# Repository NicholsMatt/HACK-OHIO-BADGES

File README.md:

# HACK-OHIO-BADGES
PCB badges for HACK OHI/O X in Autumn 2022

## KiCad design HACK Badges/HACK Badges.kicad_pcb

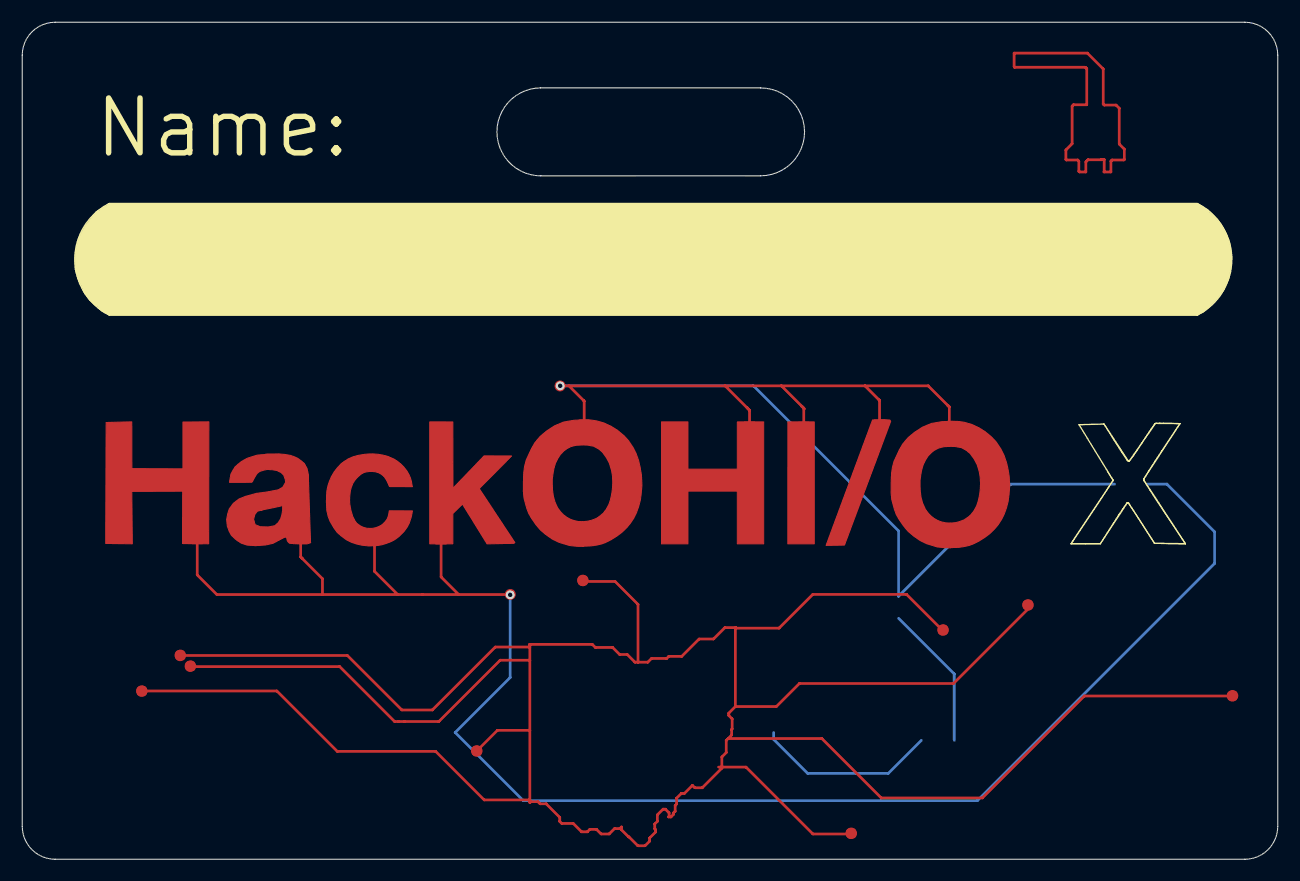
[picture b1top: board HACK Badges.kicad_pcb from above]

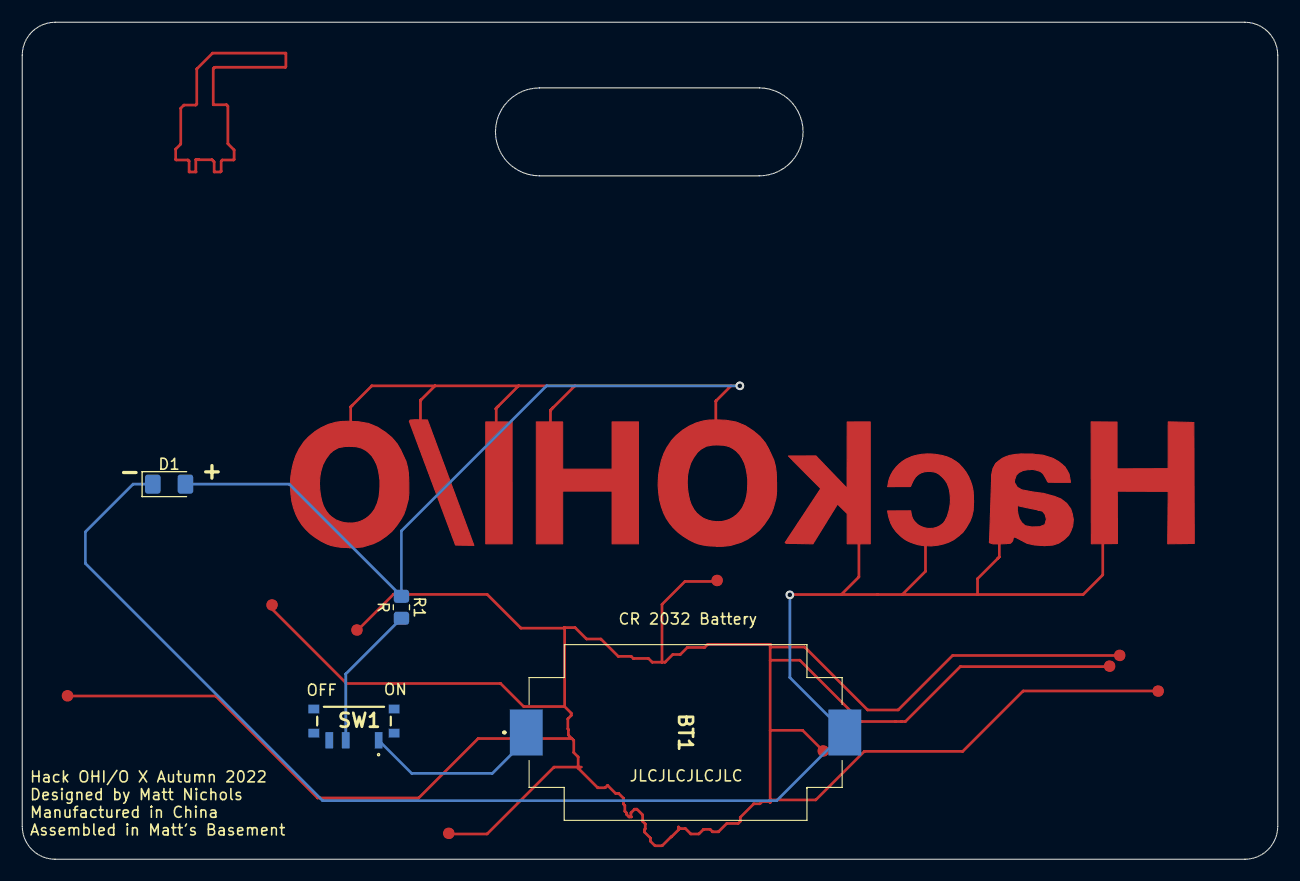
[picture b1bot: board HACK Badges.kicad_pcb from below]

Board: 2 copper layers, 114.3 x 76.2 mm, 15 parts (4 on the bottom side), 4 nets.

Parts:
BT1: Battery_Cell; CR2032BS61
D1: LED; LED_1206_3216Metric_Pad1.42x1.75mm_HandSolder
R1: R; R_0805_2012Metric_Pad1.20x1.40mm_HandSolder
SW1: SW_SPST; SSSS811101
TP1, TP2, TP3, TP4, TP5, TP6, TP7, TP8, TP9, TP10, TP11: TestPoint; TestPoint_Pad_1.0x1.0mm

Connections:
unnamed: BT1.1, SW1.1
unnamed: BT1.2, D1.1, TP1.1, TP3.1, TP4.1, TP5.1, TP6.1
unnamed: D1.2, R1.1, TP2.1, TP7.1, TP8.1, TP9.1, TP10.1, TP11.1
unnamed: R1.2, SW1.2

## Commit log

2022-09-08 Added all the files
